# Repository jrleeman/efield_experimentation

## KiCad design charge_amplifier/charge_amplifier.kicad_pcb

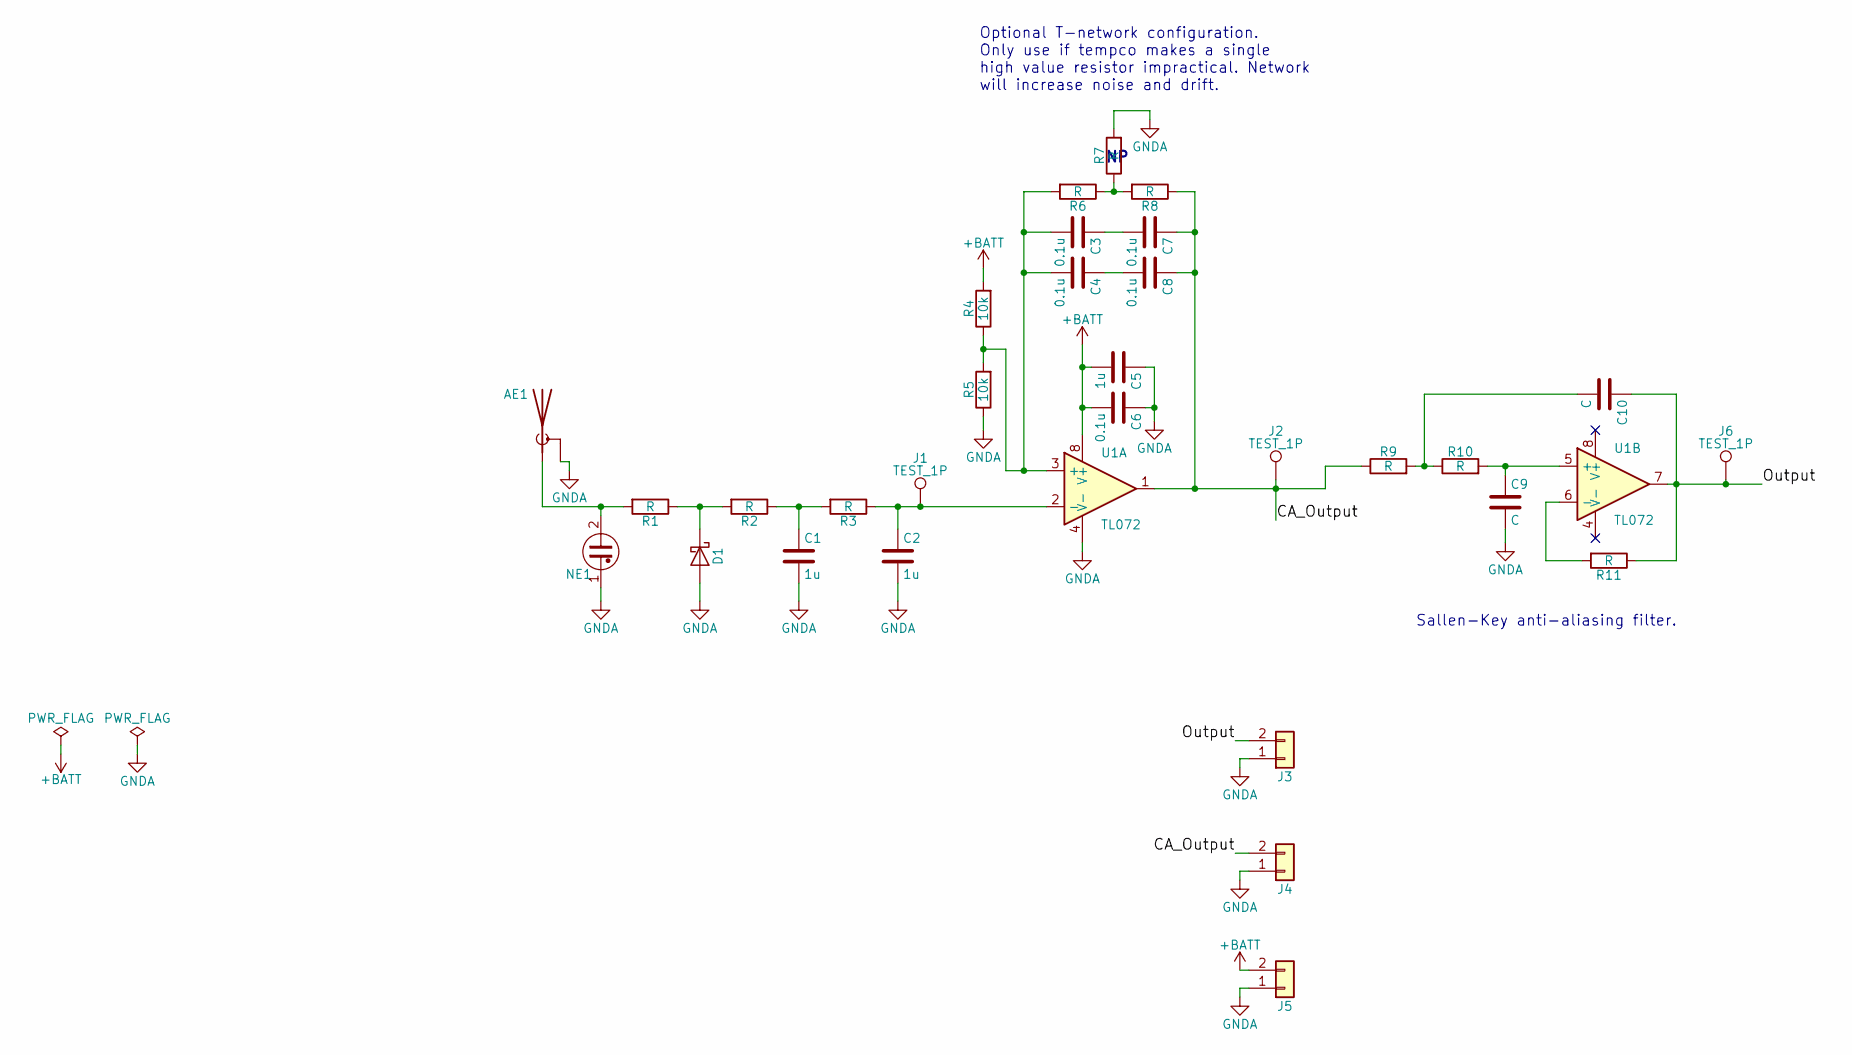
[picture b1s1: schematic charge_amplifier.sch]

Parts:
AE1: Antenna_Shield; BNC_5227677-1
C1, C2, C5: 1u; C_0603_HandSoldering; MFG Part Num Value
C3, C4, C6, C7, C8: 0.1u; C_0603_HandSoldering; MFG Part Num Value
C9, C10: C; C_0603_HandSoldering; MFG Part Num Value
D1: D_Schottky; D_SOD-323
J1, J2, J6: TEST_1P; Measurement_Point_Round-SMD-Pad_Small
J3, J4, J5: Conn_01x02; Pin_Header_Straight_1x02_Pitch2.54mm
NE1: Lamp_Neon; A1D-T; MFG Part Num A1D-T
R1, R2, R3, R6, R7, R8, R11: R; R_0603_HandSoldering
R4, R5: 10k; R_0603_HandSoldering; MFG Part Num Value
R9, R10: R; R_0603_HandSoldering; MFG Part Num Value
U1: TL072; SOIC-8-N; MFG Part Num TL072BCDR

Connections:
+BATT: C5.2, C6.2, J5.2, R4.2, U1.8 (V+)
/CA_Output: C7.1, C8.1, J2.1, J4.2, R8.1, R9.1, U1.1
/Output: C10.1, J3.2, J6.1, R11.1, U1.7
GNDA: AE1.2 (Shield), C1.2, C2.2, C5.1, C6.1, C9.2, D1.2 (A), J3.1, J4.1, J5.1, NE1.1, R5.1, R7.2, U1.4 (V-)
unnamed: AE1.1 (A), NE1.2, R1.2
unnamed: C1.1, R2.1, R3.2
unnamed: C2.1, J1.1, R3.1, U1.2 (-)
unnamed: C3.1, C7.2
unnamed: C3.2, C4.2, R4.1, R5.2, R6.2, U1.3 (+)
unnamed: C4.1, C8.2
unnamed: C9.1, R10.2, U1.5 (+)
unnamed: C10.2, R9.2, R10.1
unnamed: D1.1 (K), R1.1, R2.2
unnamed: R6.1, R7.1, R8.2
unnamed: R11.2, U1.6 (-)

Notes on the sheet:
Optional T-network configuration. Only use if tempco makes a single high value resistor impractical. Network will increase noise and drift.
Sallen-Key anti-aliasing filter.

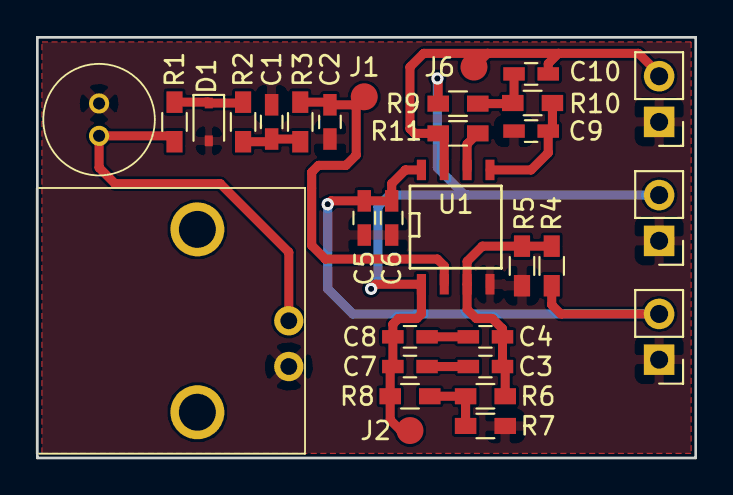
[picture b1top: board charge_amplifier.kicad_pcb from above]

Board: 2 copper layers, 36.6 x 23.4 mm, 31 parts (0 on the bottom side), 15 nets.

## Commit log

2017-11-24 Initial commit of simple charge amplifier
2017-11-24 Draft of BeagleBone connected system.
2017-11-25 Initial draft of layout
2017-11-25 finalize layout
2017-11-25 final PCB tweaks
2017-12-15 Fix schematic with bodges on Rev.A
2020-01-01 Update circuit
